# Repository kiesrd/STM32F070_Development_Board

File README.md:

# STM32F070_Development_Board
STM32F070 Development Board

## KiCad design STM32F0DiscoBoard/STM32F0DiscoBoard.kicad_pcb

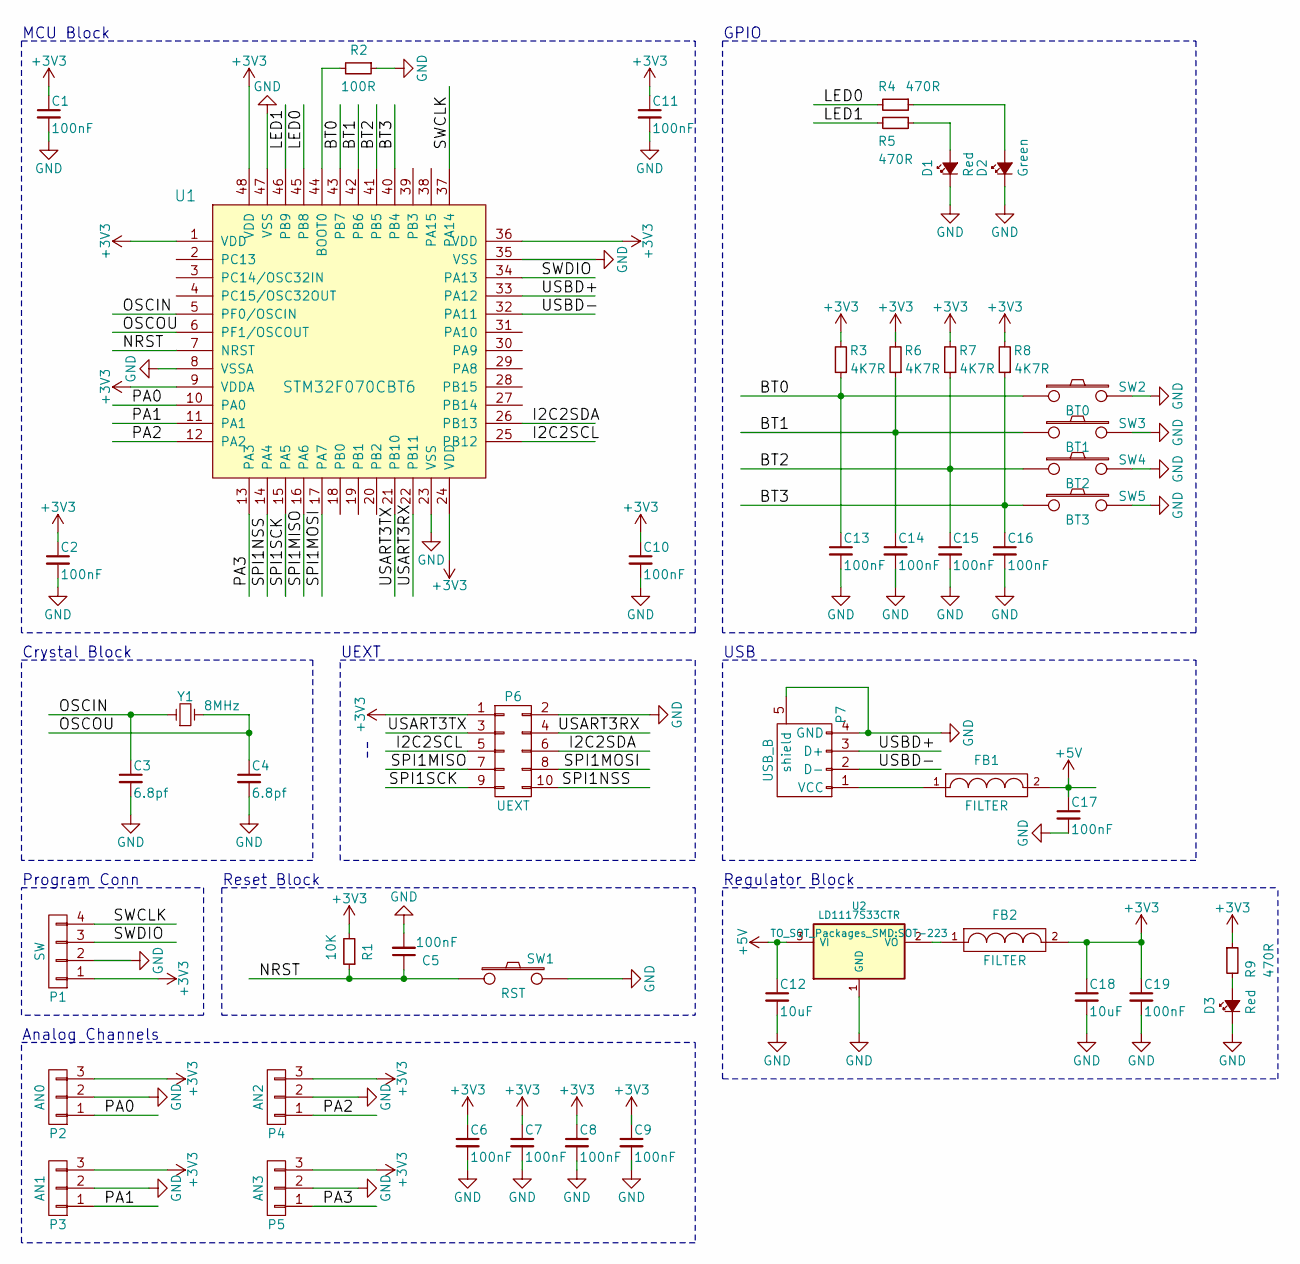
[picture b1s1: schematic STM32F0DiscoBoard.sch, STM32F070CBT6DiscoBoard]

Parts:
C1, C2, C5, C6, C7, C8, C9, C10, C11, C13, C14, C15, C16, C17, C19: 100nF; C_0603
C3, C4: 6.8pf; C_0603
C12, C18: 10uF; C_0805
D1, D3: Red; LED-0805
D2: Green; LED-0805
FB1, FB2: FILTER; R_0805_HandSoldering
P1: SW; Pin_Header_Straight_1x04
P2: AN0; Pin_Header_Straight_1x03
P3: AN1; Pin_Header_Straight_1x03
P4: AN2; Pin_Header_Straight_1x03
P5: AN3; Pin_Header_Straight_1x03
P6: UEXT; Pin_Header_Straight_2x05
P7: USB_B
R1: 10K; R_0603
R2: 100R; R_0603
R3, R6, R7, R8: 4K7R; R_0603
R4, R5, R9: 470R; R_0603
SW1: RST; SW_SPST_EVQP7C
SW2: BT0; SW_SPST_EVQP7C
SW3: BT1; SW_SPST_EVQP7C
SW4: BT2; SW_SPST_EVQP7C
SW5: BT3; SW_SPST_EVQP7C
U1: STM32F070CBT6; LQFP-48_7x7mm_Pitch0.5mm
U2: LD1117S33CTR; SOT-223
Y1: 8MHz; Q_49U3HMS

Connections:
+3V3: C1.1, C2.1, C6.1, C7.1, C8.1, C9.1, C10.1, C11.1, C18.1, C19.1, FB2.2, P1.1, P2.3, P3.3, P4.3, P5.3, P6.1, R1.2, R3.2, R6.2, R7.2, R8.2, R9.1, U1.1 (VDD), U1.9 (VDDA), U1.24 (VDD), U1.36 (VDD), U1.48 (VDD)
+5V: C12.1, C17.1, FB1.2, U2.3 (VI)
/BT0: C13.1, R3.1, SW2.1, U1.43 (PB7)
/BT1: C14.1, R6.1, SW3.1, U1.42 (PB6)
/BT2: C15.1, R7.1, SW4.1, U1.41 (PB5)
/BT3: C16.1, R8.1, SW5.1, U1.40 (PB4)
/I2C2SCL: P6.5, U1.25 (PB12)
/I2C2SDA: P6.6, U1.26 (PB13)
/LED0: R4.2, U1.45 (PB8)
/LED1: R5.2, U1.46 (PB9)
/NRST: C5.1, R1.1, SW1.1, U1.7 (NRST)
/OSCIN: C3.1, U1.5 (PF0/OSCIN), Y1.1
/OSCOU: C4.1, U1.6 (PF1/OSCOUT), Y1.2
/PA0: P2.1, U1.10 (PA0)
/PA1: P3.1, U1.11 (PA1)
/PA2: P4.1, U1.12 (PA2)
/PA3: P5.1, U1.13 (PA3)
/SPI1MISO: P6.7, U1.16 (PA6)
/SPI1MOSI: P6.8, U1.17 (PA7)
/SPI1NSS: P6.10, U1.14 (PA4)
/SPI1SCK: P6.9, U1.15 (PA5)
/SWCLK: P1.4, U1.37 (PA14)
/SWDIO: P1.3, U1.34 (PA13)
/USART3RX: P6.4, U1.22 (PB11)
/USART3TX: P6.3, U1.21 (PB10)
/USBD+: P7.3 (D+), U1.33 (PA12)
/USBD-: P7.2 (D-), U1.32 (PA11)
GND: C1.2, C2.2, C3.2, C4.2, C5.2, C6.2, C7.2, C8.2, C9.2, C10.2, C11.2, C12.2, C13.2, C14.2, C15.2, C16.2, C17.2, C18.2, C19.2, D1.1 (K), D2.1 (K), D3.1 (K), P1.2, P2.2, P3.2, P4.2, P5.2, P6.2, P7.4 (GND), P7.5 (shield), R2.1, SW1.2, SW2.2, SW3.2, SW4.2, SW5.2, U1.8 (VSSA), U1.23 (VSS), U1.35 (VSS), U1.47 (VSS), U2.1 (GND)
unnamed: D1.2 (A), R5.1
unnamed: D2.2 (A), R4.1
unnamed: D3.2 (A), R9.2
unnamed: FB1.1, P7.1 (VCC)
unnamed: FB2.1, U2.2 (VO)
unnamed: R2.2, U1.44 (BOOT0)

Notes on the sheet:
MCU Block
Crystal Block
UEXT
Program Conn
Reset Block
Analog Channels
GPIO
USB
Regulator Block

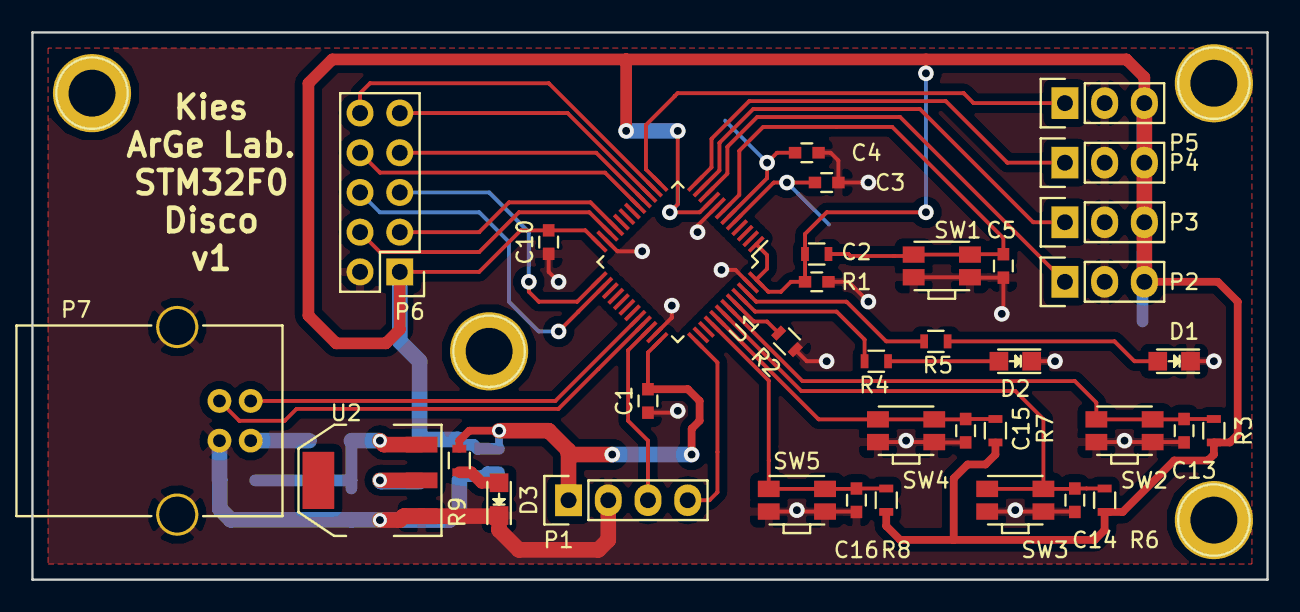
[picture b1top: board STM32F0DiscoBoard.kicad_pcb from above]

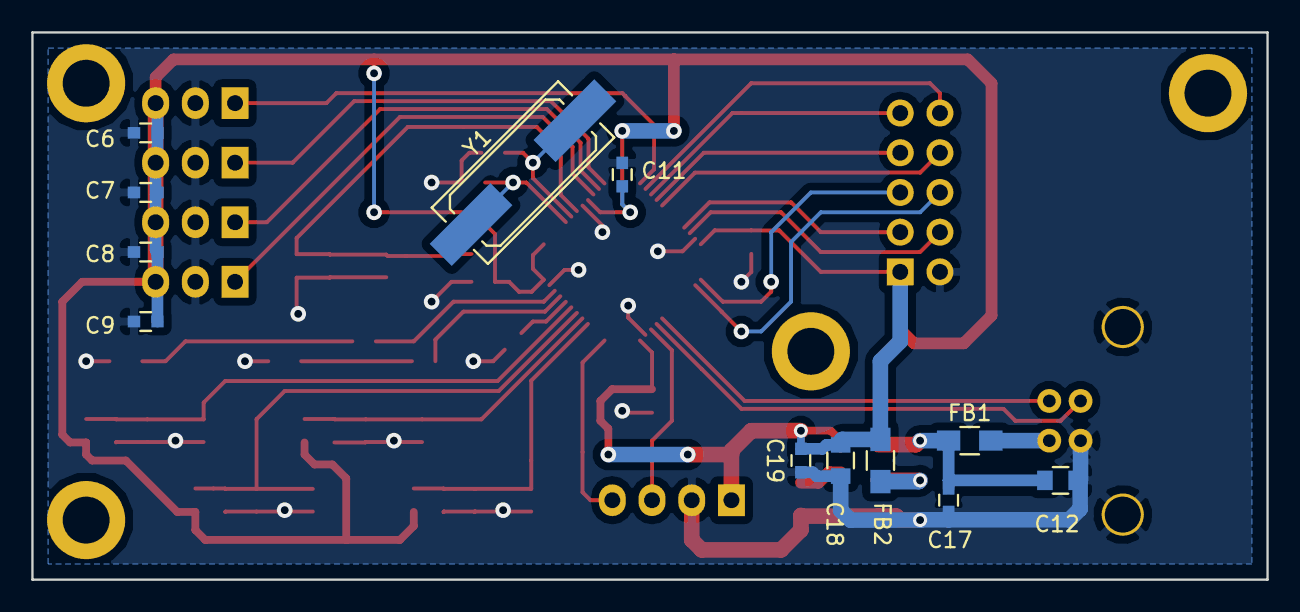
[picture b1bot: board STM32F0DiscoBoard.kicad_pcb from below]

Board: 2 copper layers, 79.0 x 35.0 mm, 48 parts (12 on the bottom side), 34 nets.

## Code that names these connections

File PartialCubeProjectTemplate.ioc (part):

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Mcu.Name=STM32F070CBTx
Mcu.Package=LQFP48
Mcu.UserName=STM32F070CBTx
PA0.Mode=IN0
PA0.Signal=ADC_IN0
PA1.Mode=IN1
PA1.Signal=ADC_IN1
PA11.Mode=Device
PA11.Signal=USB_DM
PA12.Mode=Device
PA12.Signal=USB_DP
PA13.Mode=Serial-WireDebug
PA13.Signal=SYS_SWDIO
PA14.Mode=Serial-WireDebug
PA14.Signal=SYS_SWCLK
PA2.Mode=IN2
PA2.Signal=ADC_IN2
PA3.Mode=IN3
PA3.Signal=ADC_IN3
PA4.Mode=NSS_Signal_Hard
PA4.Signal=SPI1_NSS
PA5.Mode=Full_Duplex_Master
PA5.Signal=SPI1_SCK
PA6.Mode=Full_Duplex_Master
PA6.Signal=SPI1_MISO
PA7.Mode=Full_Duplex_Master
PA7.Signal=SPI1_MOSI
PB10.Mode=Multiprocessor_communication
PB10.Signal=USART3_TX
PB11.Mode=Multiprocessor_communication
PB11.Signal=USART3_RX
PB13.Mode=I2C
PB13.Signal=I2C2_SCL
PB14.Mode=I2C
PB14.Signal=I2C2_SDA
PB4.Signal=GPIO_Input
PB5.Signal=GPIO_Input
PB6.Signal=GPIO_Input
PB7.Signal=GPIO_Input
PB8.Signal=GPIO_Output
PB9.Signal=GPIO_Output
PF0-OSC_IN.Mode=HSE-External-Oscillator
PF0-OSC_IN.Signal=RCC_OSC_IN
PF1-OSC_OUT.Mode=HSE-External-Oscillator
PF1-OSC_OUT.Signal=RCC_OSC_OUT
RCC.SYSCLKFreq_VALUE=48000000
RCC.SYSCLKSource=RCC_SYSCLKSOURCE_PLLCLK

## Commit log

2017-11-15 + KiCad project and STM Cube files
